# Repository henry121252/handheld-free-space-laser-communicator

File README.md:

# Handheld Free Space Laser Communicator

*V1.1 completed August 28th, 2026*

A handheld, battery powered free-space optical communications transceiver capable of transmitting binary data over an unguided laser beam through on-off keying.

A user types binary data with two buttons, the transceiver converts this to plaintext using ASCII. This text can be sent between transceivers.

## Specifications

* **Microcontroller:** CH32V203F8P6
* **Directionality:** Half duplex
* **Modulation:** On-off keying
* **Optical source:** Generic cheap 5mW red laser diode
* **Optical receiver:** 2x BPW34 photodiodes, MCP6007 used for transimpedance amplifiers and differential amplifier
* **Power supply:** 2S 7.4V 1000mAh LiPo bucked to +5V and +3V3 with 2x TPP00032
* **PCB:** 2-Layer custom PCB manufactured by JLCPCB

## Architecture

* **Transmitter:** Data payload is output on PA4 of the CH32 at up to ~133kb/s, a level-shifter changes the logic high output from 3V3 to 5V. This drives an IRF540 on the low side of the laser diode. The laser diode has a current limiting resistor built in, so to reduce complexity (especially with the high speed switching of the laser diode), no constant current source is used.

* **Receiver:** Two BPW34 photodiodes are located on the front of the device. The photodiode closer to the center of the device only receives ambient light. The photodiode closer to the edge of the device receives the modulated signal in addition to ambient light. Both of the photodiodes' signals are amplified with separate transimpedance amplifiers, then the ambient signal is subtracted from the data. The effect of this is that only the binary signal remains, making it much easier to resolve data. This is then fed into PA7 of the CH32 where the data is read.

## Challenges

* **Ambient light rejection:** The most obvious challenge beginning this project was how to resolve a modulated light input when its riding on some unknown, possibly changing ambient signal. As described above, this was handled through the use of a differential amplifier to subtract the ambient signal off the data.

* **Amplifier resolving power:** The gain on the transimpedance amplifiers determines not only how far the signal can be received from (due to the divergent nature of a laser diode) but also the speed at which data can be received. Too sensitive of an amplifier will saturate and lower the maximum receiver bandwidth. Too low sensitivity will lower the maximum reception distance. Because of these factors, the amplifier had to be finely tuned to maximize both bandwidth and sensitivity.
  
* **High speed data transmission and reception (hardware):** Because the device should be capable of high speed communication, any factor slowing down the rise and fall time of the transmitter had to be minimized. This meant lowering parasitic capacitances and constructing a circuit capable of quickly switching a logic level MOSFET using only a CH32 GPIO pin. In my case, the main bottleneck for these rise / fall times was caused by the MCP6007. With a 1MHz GBW and 1.9V/us slew rate, its minimum rise / fall time from 0V to +3V3 is approximately 1.5 microseconds. This meant that at a certain speed, the receiver would not be able to accurately resolve between logic high and low. Experimentation was done adjusting the speed of the transmitter until a bitrate was achieved that allowed for high speed and high accuracy reception. In my case, the minimum bit period is approximately 8 microseconds, translating to ~133kb/s.

## Additional Content

* A showcase of the transmission and reception of messages

<video src="https://github.com/user-attachments/assets/1137d4bf-9a88-49ec-ac57-38ac7f4fa6b2" controls="controls" style="max-width: 100%;">
</video>

* Hardware on the bottom of the device allows for mounting. This additional stability allows the device to transmit and receive at its maximum range.

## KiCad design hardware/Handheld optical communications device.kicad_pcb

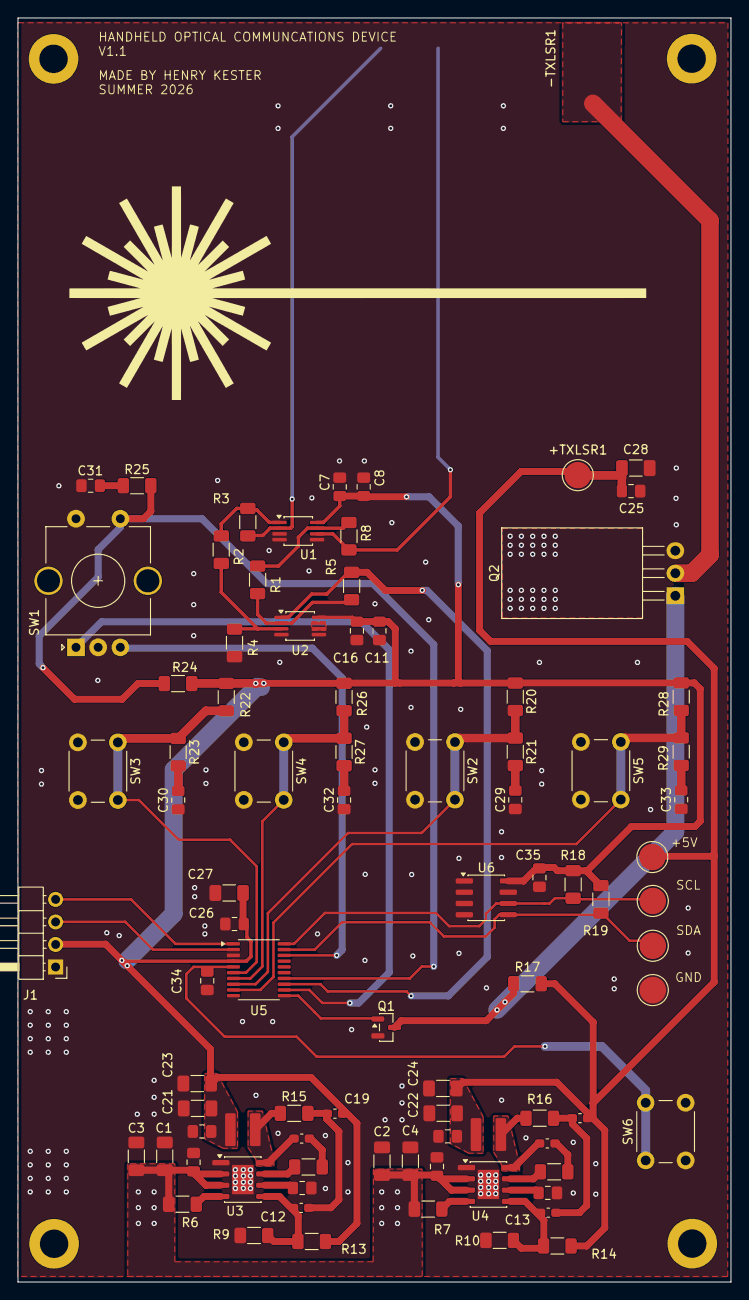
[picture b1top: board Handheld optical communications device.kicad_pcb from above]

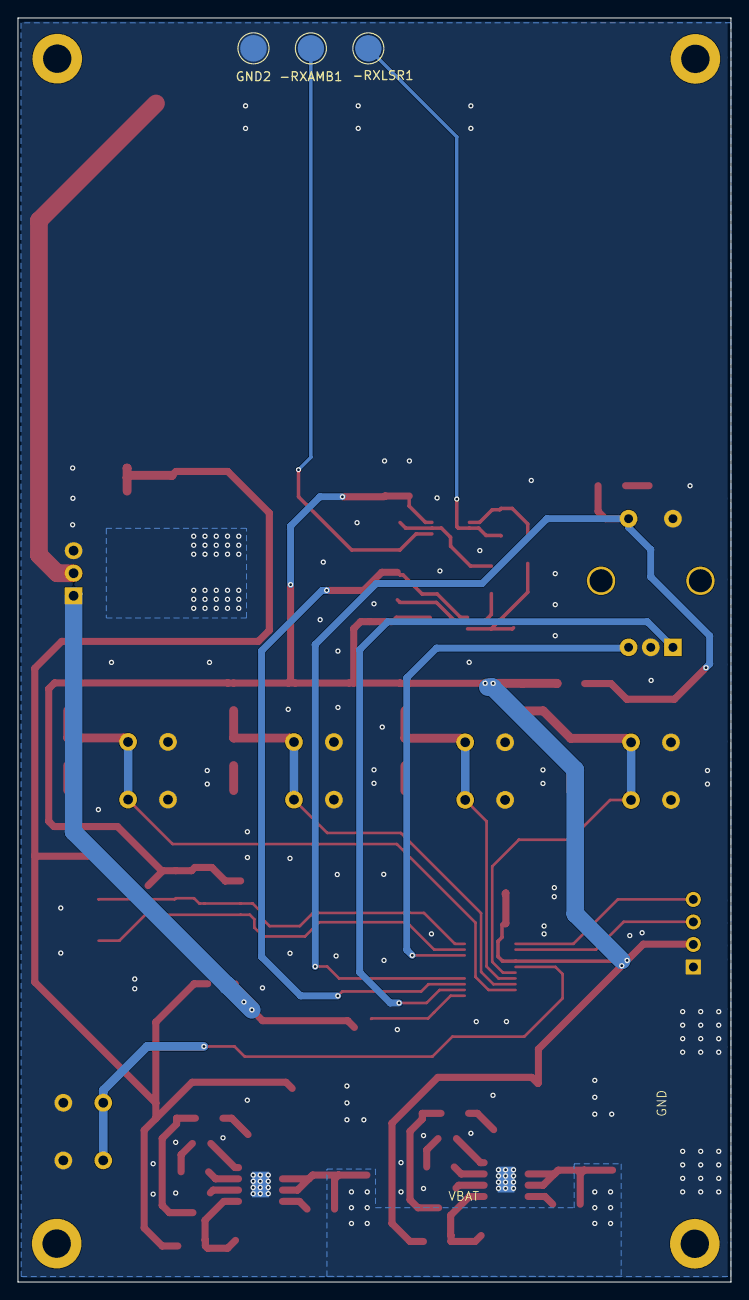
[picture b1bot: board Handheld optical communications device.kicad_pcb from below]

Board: 2 copper layers, 80.4 x 142.5 mm, 93 parts (3 on the bottom side), 45 nets.

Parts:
+5V1: TestPoint; TestPoint_Pad_D3.0mm
+TXLSR1: TestPoint; TestPoint_Pad_D3.0mm
-RXAMB1: TestPoint; TestPoint_Pad_D3.0mm
-RXLSR1: TestPoint; TestPoint_Pad_D3.0mm
C1, C2, C3, C4, C21, C22, C23, C24, C27, C28: 10u; C_1206_3216Metric_Pad1.33x1.80mm_HandSolder
C5, C6, C7, C11, C17, C18, C25, C26, C29, C30, C31, C32, C33, C34, C35: 100n; C_0805_2012Metric_Pad1.18x1.45mm_HandSolder
C8, C9, C10, C16: 1u; C_0805_2012Metric_Pad1.18x1.45mm_HandSolder
C12, C13: 33p; C_0603_1608Metric_Pad1.08x0.95mm_HandSolder
C14, C15: 47n; C_0603_1608Metric_Pad1.08x0.95mm_HandSolder
C19, C20: 10n; C_0603_1608Metric_Pad1.08x0.95mm_HandSolder
GND1, GND2: TestPoint; TestPoint_Pad_D3.0mm
H1, H2, H3, H4: MountingHole; MountingHole_3.2mm_M3_DIN965_Pad
J1: Conn_01x04; PinHeader_1x04_P2.54mm_Horizontal
L1, L2: 22u; NRS4018T220MDGJ
Q1: MMBT3904; SOT-23
Q2: IRF540N; TO-220-3_Horizontal_TabDown
R1, R2, R17: 470; R_1206_3216Metric_Pad1.30x1.75mm_HandSolder
R3, R8: 47k; R_1206_3216Metric_Pad1.30x1.75mm_HandSolder
R4, R5: 2.2k; R_1206_3216Metric_Pad1.30x1.75mm_HandSolder
R6: 10k; R_1206_3216Metric_Pad1.30x1.75mm_HandSolder
R7: 15k; R_1206_3216Metric_Pad1.30x1.75mm_HandSolder
R9: 1.2k; R_1206_3216Metric_Pad1.30x1.75mm_HandSolder
R10: 1k; R_1206_3216Metric_Pad1.30x1.75mm_HandSolder
R11, R12: 33; R_1206_3216Metric_Pad1.30x1.75mm_HandSolder
R13: 2k; R_1206_3216Metric_Pad1.30x1.75mm_HandSolder
R14: 3k; R_1206_3216Metric_Pad1.30x1.75mm_HandSolder
R15, R16: 33k; R_1206_3216Metric_Pad1.30x1.75mm_HandSolder
R18, R19, R20, R22, R24, R26, R28: 4.7k; R_1206_3216Metric_Pad1.30x1.75mm_HandSolder
R21, R23, R25, R27, R29: 100; R_1206_3216Metric_Pad1.30x1.75mm_HandSolder
SCL1: TestPoint; TestPoint_Pad_D3.0mm
SDA1: TestPoint; TestPoint_Pad_D3.0mm
SW1: RotaryEncoder_Switch; RotaryEncoder_Alps_EC11E-Switch_Vertical_H20mm_CircularMoun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
SW2, SW3, SW4, SW5, SW6: SW_Push_Dual; SW_PUSH_6mm
U1, U2: MCP6007; MSOP-8_3x3mm_P0.65mm
U3, U4: TPP00032; TPP00032-ES1R
U5: CH32V203F8P6; TSSOP-20_4.4x6.5mm_P0.65mm
U6: AT24CS64-SSHM; SOIC-8_3.9x4.9mm_P1.27mm

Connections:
+3V3: C7.1, C8.1, C11.1, C16.1, C17.1, C19.2, C21.1, C23.1, C26.1, C27.2, C35.1, J1.2, L1.1, R13.1, R18.1, R19.1, R20.1, R22.1, R24.2, R26.1, R28.1, U1.8, U2.8, U5.4 (VDD), U6.8 (VCC)
+5V: +5V1.1 (1_1), +TXLSR1.1 (1_1), C18.1, C20.2, C22.1, C24.1, C25.1, C28.2, L2.1, R14.1, R17.1
/NRST: C34.2, SW6.1, U5.5 (NRST)
/PA0: R22.2, R23.1, SW3.1, U5.6 (PA0)
/PA1: R26.2, R27.1, SW4.1, U5.7 (PA1)
/PA2: R20.2, R21.1, SW2.1, U5.8 (PA2)
/PA3: R28.2, R29.1, SW5.1, U5.9 (PA3)
/PA4: Q1.1 (B), U5.11 (PA4)
/PA5: SW1.A, U5.12 (PA5)
/PA7: R5.2, U2.1, U5.13 (PA7)
/PA8: SW1.B, U5.18 (PA8)
/PA9: R19.2, SDA1.1 (1_1), U5.19 (PA9), U6.5 (SDA)
/PA10: R18.2, SCL1.1 (1_1), U5.20 (PA10), U6.6 (SCL)
/PB0: R24.1, R25.2, SW1.S1, U5.14 (PB0)
/PB6: J1.4, U5.1 (PB6)
/PB7: J1.3, U5.2 (PB7)
AMB: R1.1, R8.2, U1.7
GND: C1.1, C2.1, C3.1, C4.1, C5.1, C6.1, C7.2, C8.2, C9.2, C10.2, C11.2, C16.2, C17.2, C18.2, C21.2, C22.2, C23.2, C24.2, C25.2, C26.2, C27.1, C28.1, C29.1, C30.1, C31.2, C32.1, C33.1, C34.1, C35.2, GND1.1 (1_1), GND2.1 (1_1), J1.1, Q1.2 (E), Q2.3 (S), R4.2, R9.2, R10.2, SW1.C, SW1.S2, SW2.2, SW3.2, SW4.2, SW5.2, SW6.2, U1.3, U1.4, U1.5, U2.4, U2.5, U3.1 (GND), U3.9 (TAB), U4.1 (GND), U4.9 (TAB), U5.3 (VSS), U6.1 (A0), U6.2 (A1), U6.3 (A2), U6.4 (GND), U6.7 (WP)
LSR: R2.1, R3.2, U1.1
unnamed: -RXAMB1.1 (1_1), R8.1, U1.6
unnamed: -RXLSR1.1 (1_1), R3.1, U1.2
unnamed: C12.1, C19.1, R15.1
unnamed: C13.1, C20.1, R16.1
unnamed: C14.2, R11.2
unnamed: C15.2, R12.2
unnamed: C29.2, R21.2
unnamed: C30.2, R23.2
unnamed: C31.1, R25.1
unnamed: C32.2, R27.2
unnamed: C33.2, R29.2
unnamed: Q1.3 (C), Q2.1 (G), R17.2
unnamed: R1.2, R5.1, U2.2
unnamed: R2.2, R4.1, U2.3
unnamed: U2.6, U2.7
unnamed: R11.1, U3.7 (BST)
unnamed: C12.2, R9.1, R13.2, U3.5 (FB)
unnamed: R6.2, U3.4 (RON)
unnamed: C9.1, U3.6 (VCC)
unnamed: R12.1, U4.7 (BST)
unnamed: C13.2, R10.1, R14.2, U4.5 (FB)
unnamed: R7.2, U4.4 (RON)
unnamed: C10.1, U4.6 (VCC)
SW1: C15.1, L2.2, R16.2, U4.8 (SW)
SW2: C14.1, L1.2, R15.2, U3.8 (SW)
VBAT: C1.2, C2.2, C3.2, C4.2, C5.2, C6.2, R6.1, R7.1, U3.2 (VIN), U3.3 (UVLO), U4.2 (VIN), U4.3 (UVLO)

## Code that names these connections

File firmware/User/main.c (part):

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#include "at24c64.h"

/* Pin Definitions -----------------------------------------------------------*/
#define B0_Pin          GPIO_Pin_1   // PA1: '1' Button
#define B1_Pin          GPIO_Pin_0   // PA0: '0' Button
#define B2_Pin          GPIO_Pin_2   // PA2: Backspace Button
#define B4_Pin          GPIO_Pin_3   // PA3: Transmit Button
#define LED_Pin         GPIO_Pin_4   // PA4: Optical TX LED
#define ENCODER_A_PIN   GPIO_Pin_5   // PA5: Rotary Encoder A
#define RX_Pin          GPIO_Pin_7   // PA7: Optical RX Signal
#define ENCODER_B_PIN   GPIO_Pin_8   // PA8: Rotary Encoder B
#define SOFT_SDA_PIN    GPIO_Pin_9   // PA9: Software I2C SDA
#define SOFT_SCL_PIN    GPIO_Pin_10  // PA10: Software I2C SCL
#define ENCODER_BTN_PIN GPIO_Pin_0   // PB0: Rotary Encoder Push Button

#define LED_Port        GPIOA

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    GPIO_InitStructure.GPIO_Mode = GPIO_Mode_IPU;
    GPIO_Init(GPIOA, &GPIO_InitStructure);

    // PA7 Optical RX Signal (Input Pull-Down)
    GPIO_InitStructure.GPIO_Pin = RX_Pin;
    GPIO_InitStructure.GPIO_Mode = GPIO_Mode_IPD;
    GPIO_Init(GPIOA, &GPIO_InitStructure);

    // Rotary Encoder Push Button (PB0)
    GPIO_InitStructure.GPIO_Pin = ENCODER_BTN_PIN;
    GPIO_InitStructure.GPIO_Mode = GPIO_Mode_IPU;
    GPIO_Init(GPIOB, &GPIO_InitStructure);
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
